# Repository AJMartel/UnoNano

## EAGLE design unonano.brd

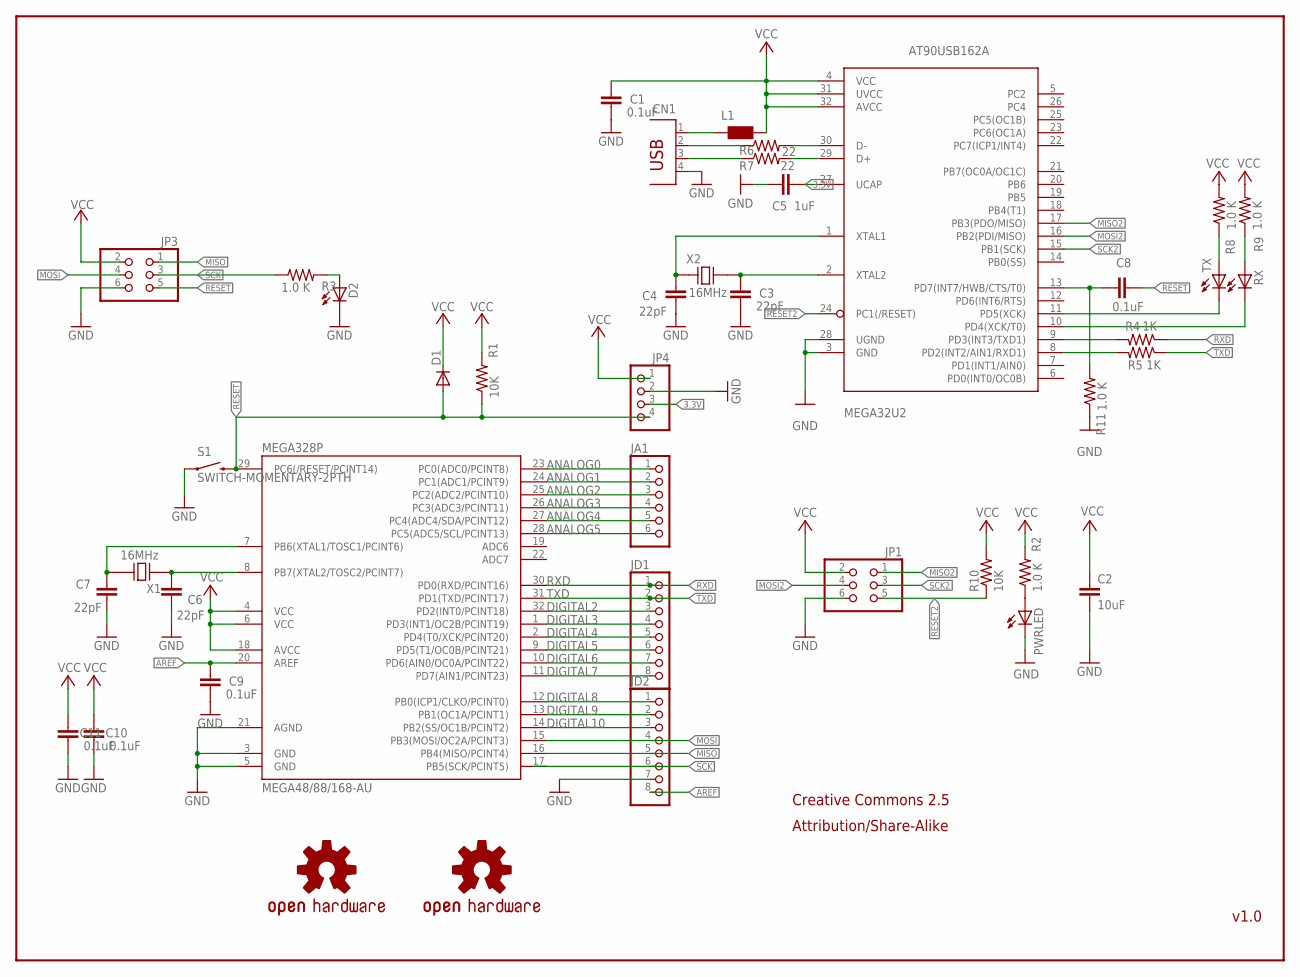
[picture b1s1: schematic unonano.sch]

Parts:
C1, C8, C9, C10, C11: 0.1uF; 0805
C2: 10uF; 1206
C3, C4, C6, C7: 22pF; 0805
C5: 1uF; 0805
CN1: PN61729
D1: DIODESOD; SOD-323
D2: Green; CHIP-LED0805
JA1: PINHD-1X6CB; 1X06-CLEANBIG
JD1, JD2: PINHD-1X8CLEANBIG; 1X08-CLEANBIG
JP1, JP3: PINHD-2X3; 2X03
JP4: PINHD-1X4CB; 1X04-CB
L1: WE-CBF; 1812
LOGO1: OSHW-LOGOL; OSHW-LOGO-L
LOGO2: OSHW-LOGOS; OSHW-LOGO-S
MEGA32U2: AT90USB162A; TQFP32-08
MEGA328P: MEGA48/88/168-AU; TQFP32-08
PWRLED: LEDCHIP-LED0805; CHIP-LED0805
R1, R10: 10K; 0805
R2, R3, R8, R9, R11: 1.0 K; 0805
R4, R5: 1K; 0805
R6, R7: 22; 0805
RX: Green; CHIP-LED0805
S1: SWITCH-MOMENTARY-2PTH; TACTILE-PTH
TX: Green; CHIP-LED0805
X1, X2: 16MHz; FA238

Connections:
3.3V: C5.1, JP4.3, MEGA32U2.27 (UCAP)
ANALOG0: JA1.1, MEGA328P.23 (PC0(ADC0/PCINT8))
ANALOG1: JA1.2, MEGA328P.24 (PC1(ADC1/PCINT9))
ANALOG2: JA1.3, MEGA328P.25 (PC2(ADC2/PCINT10))
ANALOG3: JA1.4, MEGA328P.26 (PC3(ADC3/PCINT11))
ANALOG4: JA1.5, MEGA328P.27 (PC4(ADC4/SDA/PCINT12))
ANALOG5: JA1.6, MEGA328P.28 (PC5(ADC5/SCL/PCINT13))
AREF: C9.1, JD2.8, MEGA328P.20 (AREF)
DIGITAL2: JD1.3, MEGA328P.32 (PD2(INT0/PCINT18))
DIGITAL3: JD1.4, MEGA328P.1 (PD3(INT1/OC2B/PCINT19))
DIGITAL4: JD1.5, MEGA328P.2 (PD4(T0/XCK/PCINT20))
DIGITAL5: JD1.6, MEGA328P.9 (PD5(T1/OC0B/PCINT21))
DIGITAL6: JD1.7, MEGA328P.10 (PD6(AIN0/OC0A/PCINT22))
DIGITAL7: JD1.8, MEGA328P.11 (PD7(AIN1/PCINT23))
DIGITAL8: JD2.1, MEGA328P.12 (PB0(ICP1/CLKO/PCINT0))
DIGITAL9: JD2.2, MEGA328P.13 (PB1(OC1A/PCINT1))
DIGITAL10: JD2.3, MEGA328P.14 (PB2(SS/OC1B/PCINT2))
GND: C1.2, C2.2, C3.2, C4.1, C5.2, C6.2, C7.1, C9.2, C10.2, C11.2, CN1.4, D2.C, JD2.7, JP1.6, JP3.6, JP4.2, MEGA32U2.3 (GND), MEGA32U2.28 (UGND), MEGA328P.3 (GND), MEGA328P.5 (GND), MEGA328P.21 (AGND), PWRLED.C, R11.1, S1.1
MISO: JD2.5, JP3.1, MEGA328P.16 (PB4(MISO/PCINT4))
MISO2: JP1.1, MEGA32U2.17 (PB3(PDO/MISO))
MOSI: JD2.4, JP3.4, MEGA328P.15 (PB3(MOSI/OC2A/PCINT3))
MOSI2: JP1.4, MEGA32U2.16 (PB2(PDI/MISO))
unnamed: C7.2, MEGA328P.7 (PB6(XTAL1/TOSC1/PCINT6)), X1.3 (1)
unnamed: C6.1, MEGA328P.8 (PB7(XTAL2/TOSC2/PCINT7)), X1.1 (0)
unnamed: PWRLED.A, R2.1
unnamed: D2.A, R3.2
unnamed: CN1.2, R6.1
unnamed: CN1.3, R7.1
unnamed: MEGA32U2.9 (PD3(INT3/TXD1)), R4.2
unnamed: CN1.1, L1.1
unnamed: MEGA32U2.8 (PD2(INT2/AIN1/RXD1)), R5.2
unnamed: C8.1, MEGA32U2.13 (PD7(INT7/HWB/CTS/T0)), R11.2
unnamed: MEGA32U2.30 (D-), R6.2
unnamed: MEGA32U2.29 (D+), R7.2
unnamed: C3.1, MEGA32U2.2 (XTAL2), X2.3 (1)
unnamed: R8.1, TX.A
unnamed: R9.1, RX.A
unnamed: MEGA32U2.11 (PD5(XCK)), TX.C
unnamed: MEGA32U2.10 (PD4(XCK/T0)), RX.C
unnamed: C4.2, MEGA32U2.1 (XTAL1), X2.1 (0)
RESET: C8.2, D1.2 (A), JP3.5, JP4.4, MEGA328P.29 (PC6(/RESET/PCINT14)), R1.1, S1.3 (2)
RESET2: JP1.5, MEGA32U2.24 (PC1(/RESET)), R10.1
RXD: JD1.1, MEGA328P.30 (PD0(RXD/PCINT16)), R4.1
SCK: JD2.6, JP3.3, MEGA328P.17 (PB5(SCK/PCINT5)), R3.1
SCK2: JP1.3, MEGA32U2.15 (PB1(SCK))
TXD: JD1.2, MEGA328P.31 (PD1(TXD/PCINT17)), R5.1
VCC: C1.1, C2.1, C10.1, C11.1, D1.1 (C), JP1.2, JP3.2, JP4.1, L1.2, MEGA32U2.4 (VCC), MEGA32U2.31 (UVCC), MEGA32U2.32 (AVCC), MEGA328P.4 (VCC), MEGA328P.6 (VCC), MEGA328P.18 (AVCC), R1.2, R2.2, R8.2, R9.2, R10.2

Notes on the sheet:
v1.0
Creative Commons 2.5
Attribution/Share-Alike

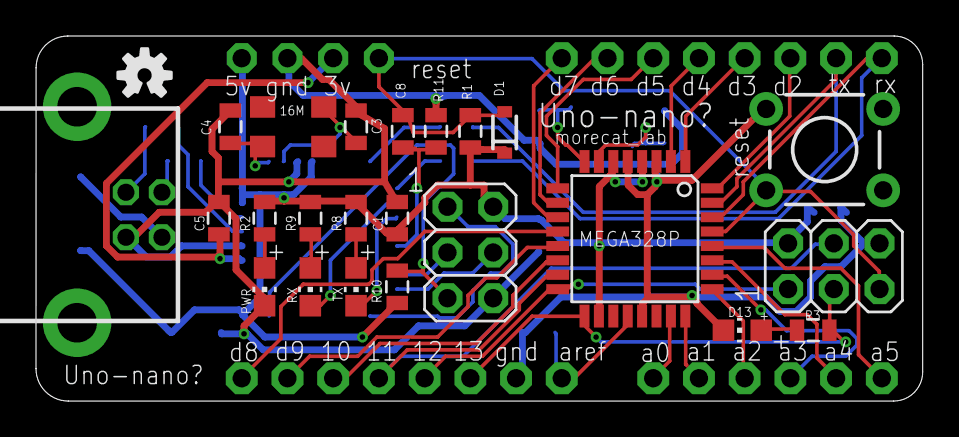
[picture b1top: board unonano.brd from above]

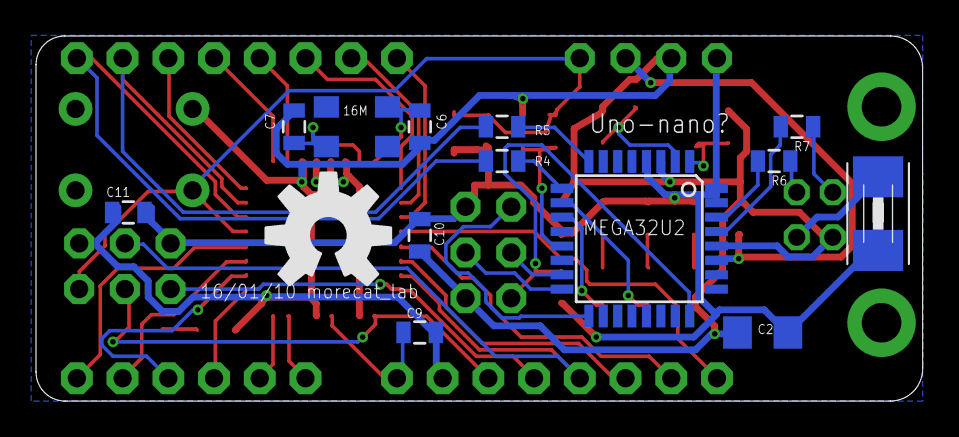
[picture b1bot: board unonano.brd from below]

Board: 2 copper layers, 49.3 x 20.3 mm, 42 parts (14 on the bottom side), 47 nets.

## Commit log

2017-08-03 initial commit
    make initial design public
2017-08-03 add images of schematic and board layout

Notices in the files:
parts and their libraries:
SparkFun-Capacitors: Licensing: CC v3.0 Share-Alike You are welcome to use this library for commercial purposes.
SparkFun-Electromechanical: Licensing: Creative Commons ShareAlike 4.0 International - https://creativecommons.org/licenses/by-sa/4.0
